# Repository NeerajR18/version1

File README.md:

# version1

version1 is a TKL(TenKeyLess) Mechanical Keyboard with Kalih Hotswappable sockets and Cherry MX Black switches.

The keyboard features a fully custom made PCB with 87 standard TKL keys and 4 macrokeys. The keyboard is wired, using a USB-C port.
version1 uses the STM32F072CBT6 at its core.

The PCB was designed in KiCad and the case was designed in Autodesk Fusion. Fusion was also used to render images of the design.
The footprints for the switches have been taken from the marbastlib library - https://github.com/ebastler/marbastlib

Made for Hack Club Fallout.
Note: This is still a WIP. Please copy anything at your own risk or do not copy at all.
## Why build this?
This keyboard was designed as a deep dive into electronics as a beginner and to learn more about CAD. 

I also have never used mechanical keyboards, so I want this to act as my entry point to mechanical keyboards.

## Repository Guide
```
version1/
|── PCB/
|   |── version1.kicad_pro
|   |── version1.kicad_pcb
|   |── version1.kicad_sch
|   └── version1_matrix.kicad_sch
|
|── CAD/
|   |── version1.f3d
|   |── version1-assembly.step
|   |── version1.fbx
|   |
|   |──── version1-base/
|   |     |── version1-base-left.step
|   |     |── version1-base-middle.step
|   |     └── version1-base-right.step
|   |
|   └──── version1-plate/
|         |── version1-plate-left.step
|         └── version1-plate-right.step
| 
|── Production/   
|    |── gerbers.zip/
|    |
|    |── STL Files/
|    |   |─── version1-base/
|    |   |    |── version1-base-left.stl
|    |   |    |── version1-base-middle.stl
|    |   |    └── version1-base-right.stl
|    |   |
|    |   └─── version1-plate/
|    |        |── version1-plate-left.stl
|    |        └── version1-plate-right.stl
|    |
|    └── STEP Files/
|           |─── version1-base/
|           |      |── version1-base-left.step
|           |      |── version1-base-middle.step
|           |      └── version1-base-right.step
|           |
|           └──── version1-plate/
|                   |── version1-plate-left.step
|                   └── version1-plate-right.step
|
|── Assets/
|    |── Keycaps/
|    |── MX Switch/
|    |── Rotary Encoder/
|    |── Type-C/
|    └── version1.fbx
|
|── qmk_firmware/
|    └── version1/
|       |── keymaps/
|       |   └── keymaps/
|       |       └── default/
|       |           └── keymap.c
|       |── config.h
|       |── keyboard.json
|       └── readme.md
|
|── BOM.csv
|── Zine.pdf
└── README.md
```

## Schematic
##### Overall Schematic

##### Key matrix

## PCB
##### PCB Front without GND Plane

##### PCB Front with GND Plane

##### PCB Back without GND Plane

##### PCB Back with GND Plane

## CAD
The case has been split into two parts on the plate and 3 parts on the base to accomodate 3D printed parts. The plates and base have small pegs and holes for assembly.

#### Full Assembly
##### Top View

#####  Side View

#### Top Plate
##### Top View

#####  Side View

#### Base
##### Top View

#####  Side View

## Renders 
##### Top view

##### Side view

## Build Guide
To be updated with pictures after IRL build.

## Bill of Materials

| MPN | Designator | Quantity | Unit Price (USD) | Price (Ext.) | Package | LCSC Part Number | Link |
|-----|------------|----------|-----------------|--------------|---------|-----------------|------|
| CPG151101S11-2 | MX1-M91 | 100 | 0.0344 | 3.44 | - | C49352235 | https://www.lcsc.com/product-detail/C49352235.html |
| STM32F072CBT6 | U1 | 1 | 2.212 | 2.21 | LQFP-48(7x7) | C81720 | https://www.lcsc.com/product-detail/C81720.html |
| XC6206P332MR-G | U2 | 5 | 0.1119 | 0.56 | SOT-23-3L | C5446 | https://www.lcsc.com/product-detail/C5446.html |
| PRTR5V0U2X-ES | D1 | 5 | 0.0404 | 0.2 | SOT-143 | C5180302 | https://www.lcsc.com/product-detail/C5180302.html |
| 1N4148W | D2-D93 | 100 | 0.0058 | 0.58 | SOD-123 | C917030 | https://www.lcsc.com/product-detail/C917030.html |
| TYPE-C 16PIN 2MD(073) | J1 | 20 | 0.0747 | 1.49 | SMD | C2765186 | https://www.lcsc.com/product-detail/C2765186.html |
| TS-1088-AR02016 | SW1, SW2 | 10 | 0.0538 | 0.54 | SMD, 4x3mm | C720477 | https://www.lcsc.com/product-detail/C720477.html |
| EC11E15244B2 | SW3 | 1 | 2 | 2 | Through Hole | C470754 | https://www.lcsc.com/product-detail/C470754.html |
| 1206L050YR | F1 | 10 | 0.0622 | 0.62 | 1206 | C163512 | https://www.lcsc.com/product-detail/C163512.html |
| RC0402FR-075K1L | R1, R2 | 100 | 0.0009 | 0.09 | 0402 | C105872 | https://www.lcsc.com/product-detail/C105872.html |
| RC0402FR-0710KL | R3 | 100 | 0.0008 | 0.08 | 0603 | C60490 | https://www.lcsc.com/product-detail/C60490.html |
| CC0402KRX7R7BB104 | C1, C4, C5, C6, C7, C8, C10 | 100 | 0.0011 | 0.11 | 0402 | C60474 | https://www.lcsc.com/product-detail/C60474.html |
| CL10B105KA8NNNC | C2, C3 | 50 | 0.0069 | 0.35 | 0603 | C29936 | https://www.lcsc.com/product-detail/C29936.html |
| CL10A106KP8NNNC | C9 | 50 | 0.0103 | 0.52 | 0603 | C19702 | https://www.lcsc.com/product-detail/C19702.html |
| Cherry MX Black Switches [Pack of 10] | - | 10 | 3.48 | 34.8 | - | - | https://neomacro.in/products/cherry-mx-switches?_pos=2&_sid=a9445e82d&_ss=r&variant=47150319108374 |
| Keycaps | - | 1 | 13.5 | 13.5 | - | - | https://stackskb.com/store/veekos-gradient-keycaps-cherry-profile-135-keys/ |
| Stabilizers (clip in) | - | 10 | 0.33 | 3.32 | - | - | https://neomacro.in/products/cherry-pcb-mount-stabilizers-clip-in?_pos=1&_sid=0547a7463&_ss=r |
| Wires for stabilizers | - | 1 | 4.16 | 4.16 | - | - | https://neomacro.in/products/equalz-c3-stabilizer-wire-set |
| M3x20mm Screws | - | 15 | 0.017 | 0.26 | - | - | https://omrook.com/ss-allen-csk-m3-x-20mm-dia-3mm-length-20mm-stainless-steel-ss202-allen-socket-countersunk-screws/ |
| M3x4 Brass Inserts | - | 50 | 0.023 | 1.15 | - | - | https://omrook.com/m3-x-4-brass-threaded-inserts-nut-50pc/ |
| Rotary Encoder Knob [Pack of 5] | - | 1 | 0.033 | 0.17 | - | - | https://makerbazar.in/products/black-rotary-encoder-knob-111-no |
| 1x4 Right Angle Berg Pin Header 2.54 mm pitch | J2 | 5 | 0.041 | 0.21 | - | - | https://sharvielectronics.com/product/4x1-4pin-male-right-angle-berg-header-connector-6mm-2-54mm-pitch/ |
| PCB - JLCPCB (with shipping) | - | 5 | 9.552 | 47.76 | - | - | https://jlcpcb.com/ |
| Total |  |  |  | 118.12 |  |  |  |

## Extras
### To be added in the future
- Angle adjustment
- Better case

### Resources I used for making this
- GrabCAD - https://grabcad.com/ [3D Models]
- marbastlib library - https://github.com/ebastler/marbastlib
- Noah Kiser on youtube - https://www.youtube.com/@noahkiser
- Keyboard Layout Editor - https://www.keyboard-layout-editor.com/
- ai03 Plate Generator - https://kbplate.ai03.com/
- MECH-TKL on cults3d - https://cults3d.com/en/3d-model/gadget/mechanical-keyboard-mech-tkl
- KiCad - https://www.kicad.org
- Keyboard Atelier discord server
- Autodesk Fusion - https://www.autodesk.com/products/fusion-360/personal
- Modern Hobbyist on YouTube - https://www.youtube.com/watch?v=u13yRbBiRYM
- iNimbleSloth on YouTube - https://www.youtube.com/watch?v=9bjp_LteX_Y
- Joe Scotto on YouTube - https://www.youtube.com/watch?v=o7SF2TPVV6o
- Hack Club and Fallout for funding - https://hackclub.com/
                                    - https://fallout.hackclub.com/

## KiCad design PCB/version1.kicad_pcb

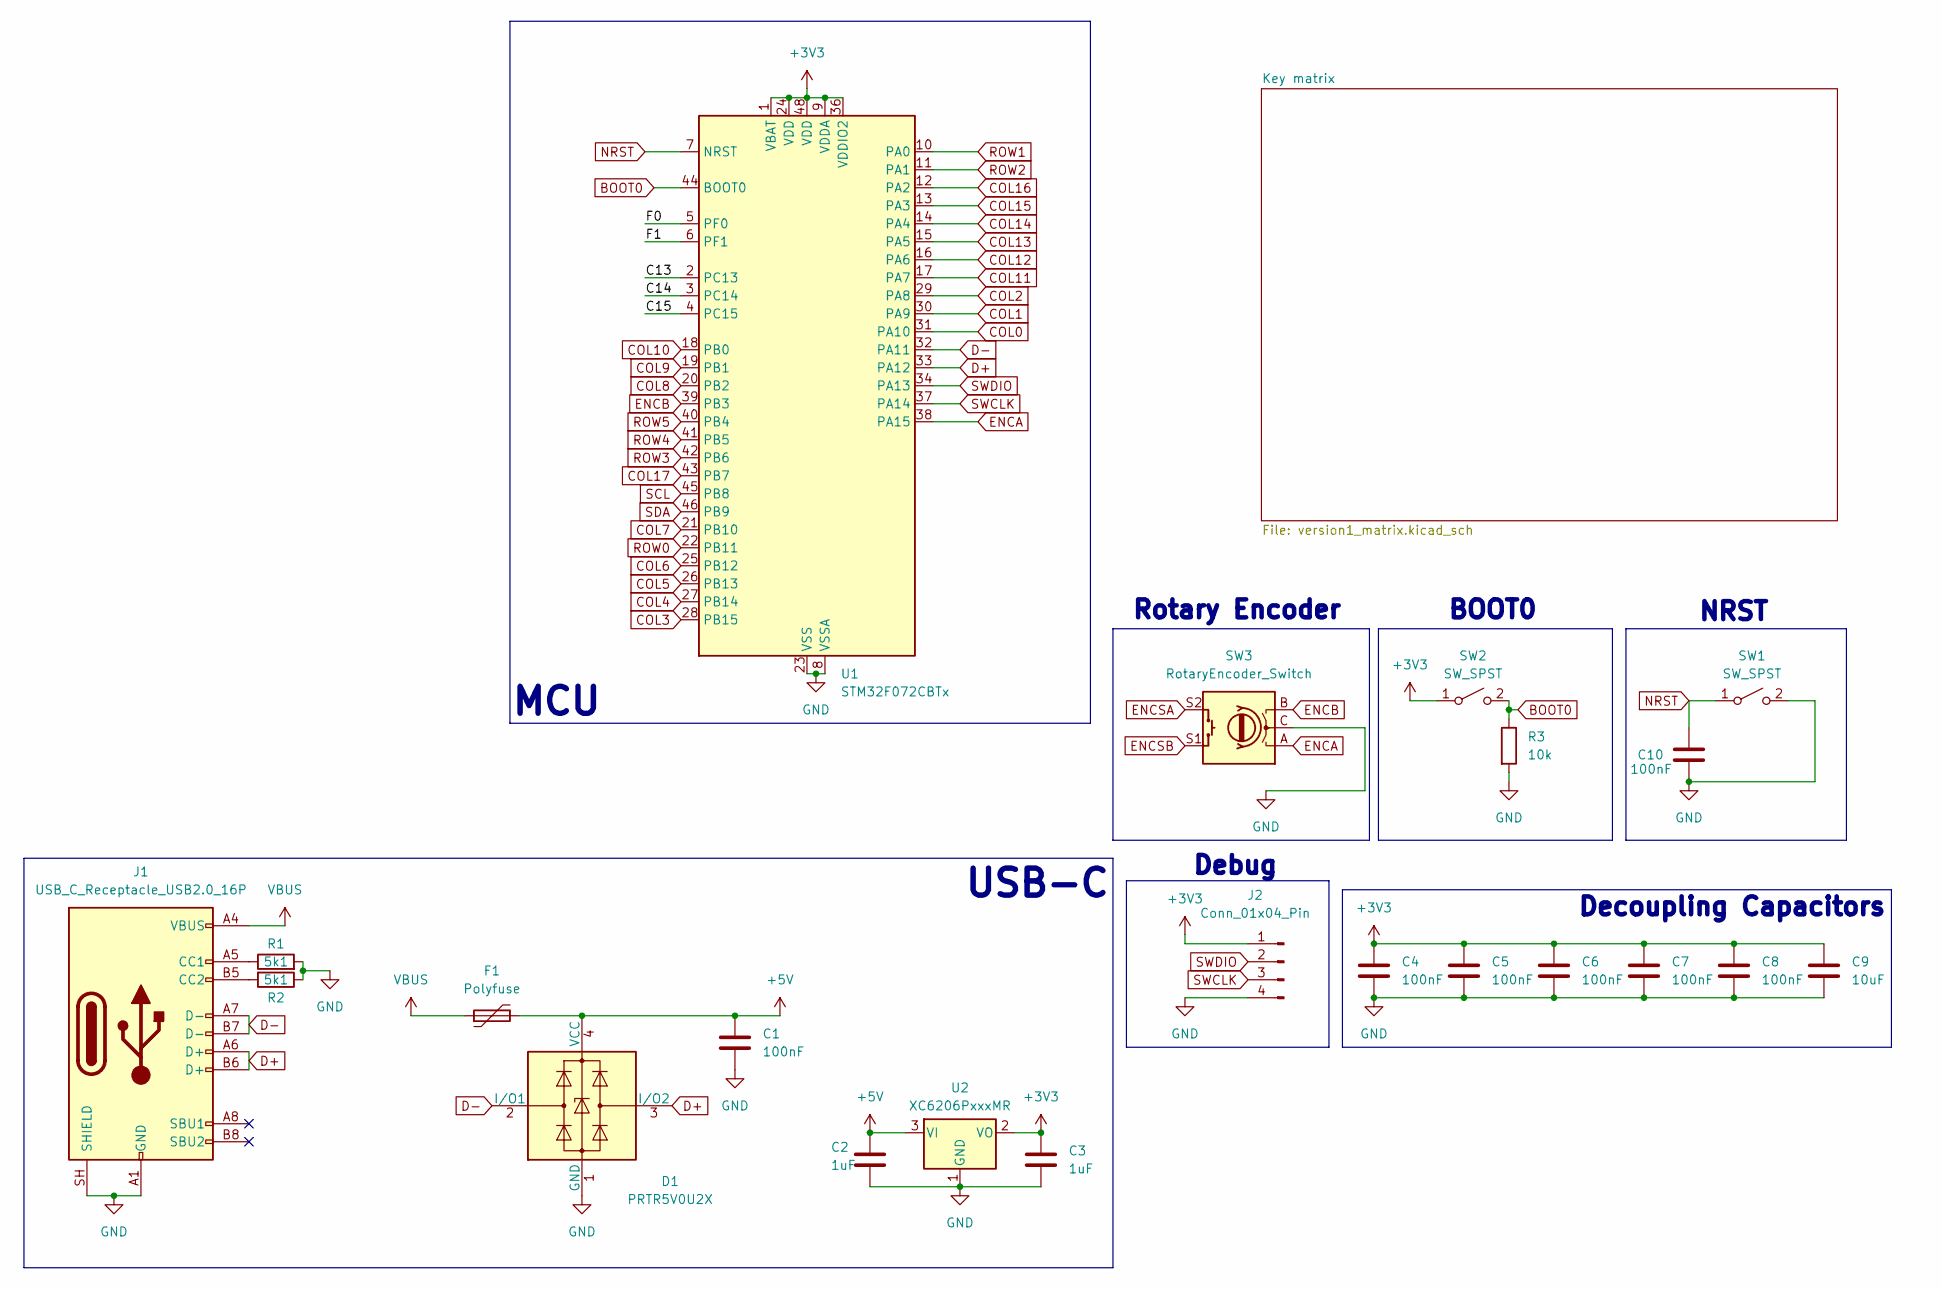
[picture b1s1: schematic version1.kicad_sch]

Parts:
C1, C4, C5, C6, C7, C8, C10: 100nF; C_0402_1005Metric
C2, C3: 1uF; C_0603_1608Metric
C9: 10uF; C_0603_1608Metric
D1: PRTR5V0U2X; SOT-143
F1: Polyfuse; Fuse_1206_3216Metric
J1: USB_C_Receptacle_USB2.0_16P; USB_C_Receptacle_HRO_TYPE-C-31-M-12
J2: Conn_01x04_Pin; PinHeader_1x04_P2.54mm_Horizontal
R1, R2: 5k1; R_0402_1005Metric
R3: 10k; R_0603_1608Metric
SW1, SW2: SW_SPST; SW_SPST_TS-1088-xR020
SW3: RotaryEncoder_Switch; RotaryEncoder_Alps_EC11E-Switch_Vertical_H20mm
U1: STM32F072CBTx; LQFP-48_7x7mm_P0.5mm
U2: XC6206PxxxMR; SOT-23-3

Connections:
+3V3: C3.1, C4.1, C5.1, C6.1, C7.1, C8.1, C9.1, J2.1, SW2.1 (A), U1.1 (VBAT), U1.9 (VDDA), U1.24 (VDD), U1.36 (VDDIO2), U1.48 (VDD), U2.2 (VO)
+5V: C1.1, C2.1, D1.4 (VCC), F1.2, U2.3 (VI)
/C13: U1.2 (PC13)
/C14: U1.3 (PC14)
/C15: U1.4 (PC15)
/F0: U1.5 (PF0)
/F1: U1.6 (PF1)
BOOT0: R3.1, SW2.2 (B), U1.44 (BOOT0)
COL0: U1.31 (PA10); also elsewhere on the board
COL1: U1.30 (PA9); also elsewhere on the board
COL2: U1.29 (PA8); also elsewhere on the board
COL3: U1.28 (PB15); also elsewhere on the board
COL4: U1.27 (PB14); also elsewhere on the board
COL5: U1.26 (PB13); also elsewhere on the board
COL6: U1.25 (PB12); also elsewhere on the board
COL7: U1.21 (PB10); also elsewhere on the board
COL8: U1.20 (PB2); also elsewhere on the board
COL9: U1.19 (PB1); also elsewhere on the board
COL10: U1.18 (PB0); also elsewhere on the board
COL11: U1.17 (PA7); also elsewhere on the board
COL12: U1.16 (PA6); also elsewhere on the board
COL13: U1.15 (PA5); also elsewhere on the board
COL14: U1.14 (PA4); also elsewhere on the board
COL15: U1.13 (PA3); also elsewhere on the board
COL16: U1.12 (PA2); also elsewhere on the board
COL17: SW3.S1, U1.43 (PB7); also elsewhere on the board
D+: D1.3 (I/O2), J1.A6 (D+), J1.B6 (D+), U1.33 (PA12)
D-: D1.2 (I/O1), J1.A7 (D-), J1.B7 (D-), U1.32 (PA11)
ENCA: SW3.A, U1.38 (PA15)
ENCB: SW3.B, U1.39 (PB3)
ENCSA: SW3.S2; also elsewhere on the board
GND: C1.2, C2.2, C3.2, C4.2, C5.2, C6.2, C7.2, C8.2, C9.2, C10.2, D1.1 (GND), J1.A1 (GND), J1.A12 (GND), J1.B1 (GND), J1.B12 (GND), J1.SH (SHIELD), J2.4, R1.2, R2.1, R3.2, SW1.2 (B), SW3.C, U1.8 (VSSA), U1.23 (VSS), U1.35 (VSS), U1.47 (VSS), U2.1 (GND)
NRST: C10.1, SW1.1 (A), U1.7 (NRST)
unnamed: J1.A5 (CC1), R1.1
unnamed: J1.B5 (CC2), R2.2
ROW0: U1.22 (PB11); also elsewhere on the board
ROW1: U1.10 (PA0); also elsewhere on the board
ROW2: U1.11 (PA1); also elsewhere on the board
ROW3: U1.42 (PB6); also elsewhere on the board
ROW4: U1.41 (PB5); also elsewhere on the board
ROW5: U1.40 (PB4); also elsewhere on the board
SCL: U1.45 (PB8)
SDA: U1.46 (PB9)
SWCLK: J2.3, U1.37 (PA14)
SWDIO: J2.2, U1.34 (PA13)
VBUS: F1.1, J1.A4 (VBUS), J1.A9 (VBUS), J1.B4 (VBUS), J1.B9 (VBUS)

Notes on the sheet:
BOOT0
Debug
MCU
Rotary Encoder
NRST
USB-C
Decoupling Capacitors

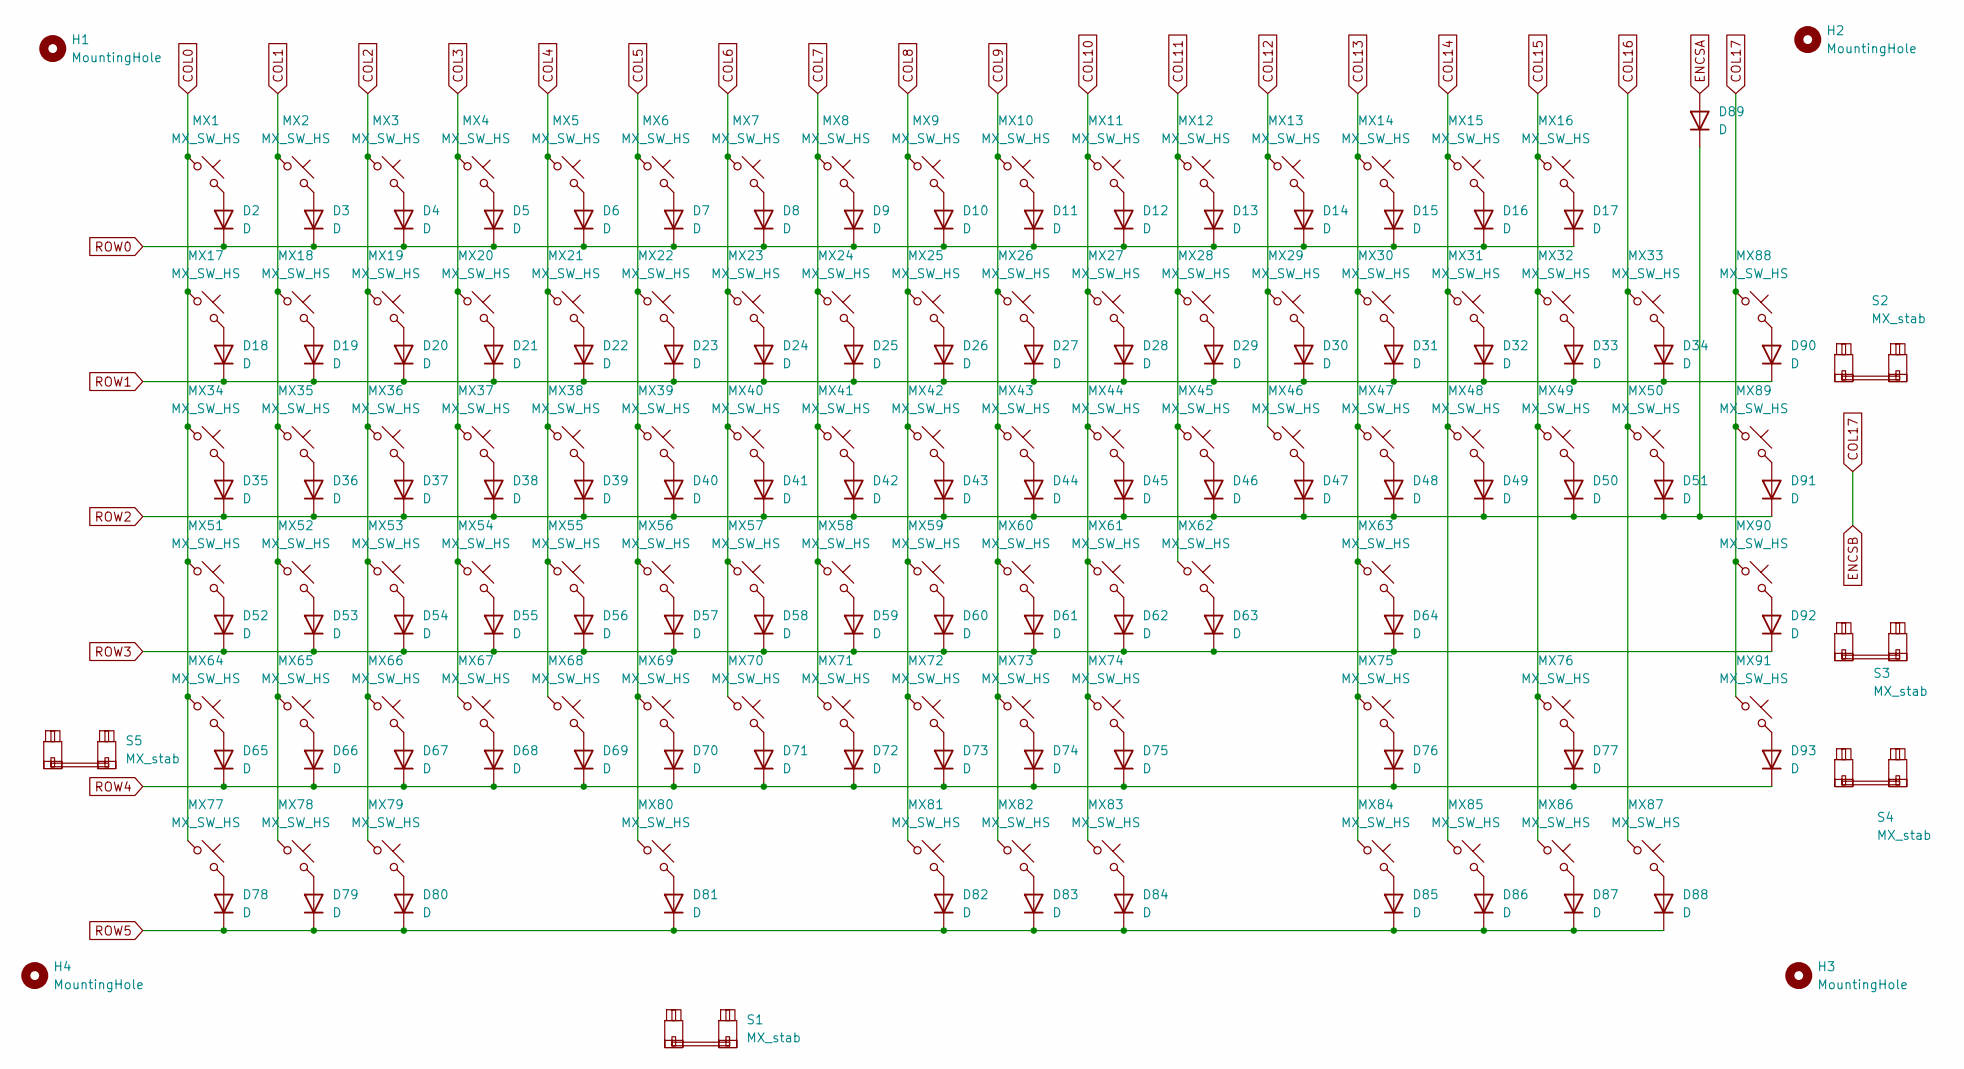
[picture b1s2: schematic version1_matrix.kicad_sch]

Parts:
D2, D3, D4, D5, D6, D7, D8, D9, D10, D11, D12, D13, D14, D15, D16, D17, D18, D19, D20, D21, D22, D23, D24, D25, D26, D27, D28, D29, D30, D31, D32, D33, D34, D35, D36, D37, D38, D39, D40, D41, D42, D43, D44, D45, D46, D47, D48, D49, D50, D51, D52, D53, D54, D55, D56, D57, D58, D59, D60, D61, D62, D63, D64, D65, D66, D67, D68, D69, D70, D71, D72, D73, D74, D75, D76, D77, D78, D79, D80, D81, D82, D83, D84, D85, D86, D87, D88, D89, D90, D91, D92, D93: D; D_SOD-123
H1, H2, H3, H4: MountingHole; MountingHole_2mm
MX1, MX2, MX3, MX4, MX5, MX6, MX7, MX8, MX9, MX10, MX11, MX12, MX13, MX14, MX15, MX16, MX17, MX18, MX19, MX20, MX21, MX22, MX23, MX24, MX25, MX26, MX27, MX28, MX29, MX30, MX31, MX32, MX33, MX35, MX36, MX37, MX38, MX39, MX40, MX41, MX42, MX43, MX44, MX45, MX46, MX48, MX49, MX50, MX52, MX53, MX54, MX55, MX56, MX57, MX58, MX59, MX60, MX61, MX62, MX63, MX64, MX65, MX66, MX67, MX68, MX69, MX70, MX71, MX72, MX73, MX74, MX75, MX76, MX80, MX85, MX86, MX87, MX88, MX89, MX90, MX91: MX_SW_HS; SW_MX_HS_CPG151101S11_1u
MX34, MX47: MX_SW_HS; SW_MX_HS_CPG151101S11_1.5u
MX51: MX_SW_HS; SW_MX_HS_CPG151101S11_1.75u
MX77, MX78, MX79, MX81, MX82, MX83, MX84: MX_SW_HS; SW_MX_HS_CPG151101S11_1.25u
S1: MX_stab; STAB_MX_6.25u
S2, S3: MX_stab; STAB_MX_2.25u
S4: MX_stab; STAB_MX_2.75u
S5: MX_stab; STAB_MX_2u

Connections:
COL0: MX1.1, MX17.1, MX34.1, MX51.1, MX64.1, MX77.1; also elsewhere on the board
COL1: MX2.1, MX18.1, MX35.1, MX52.1, MX65.1, MX78.1; also elsewhere on the board
COL2: MX3.1, MX19.1, MX36.1, MX53.1, MX66.1, MX79.1; also elsewhere on the board
COL3: MX4.1, MX20.1, MX37.1, MX54.1, MX67.1; also elsewhere on the board
COL4: MX5.1, MX21.1, MX38.1, MX55.1, MX68.1; also elsewhere on the board
COL5: MX6.1, MX22.1, MX39.1, MX56.1, MX69.1, MX80.1; also elsewhere on the board
COL6: MX7.1, MX23.1, MX40.1, MX57.1, MX70.1; also elsewhere on the board
COL7: MX8.1, MX24.1, MX41.1, MX58.1, MX71.1; also elsewhere on the board
COL8: MX9.1, MX25.1, MX42.1, MX59.1, MX72.1, MX81.1; also elsewhere on the board
COL9: MX10.1, MX26.1, MX43.1, MX60.1, MX73.1, MX82.1; also elsewhere on the board
COL10: MX11.1, MX27.1, MX44.1, MX61.1, MX74.1, MX83.1; also elsewhere on the board
COL11: MX12.1, MX28.1, MX45.1, MX62.1; also elsewhere on the board
COL12: MX13.1, MX29.1, MX46.1; also elsewhere on the board
COL13: MX14.1, MX30.1, MX47.1, MX63.1, MX75.1, MX84.1; also elsewhere on the board
COL14: MX15.1, MX31.1, MX48.1, MX85.1; also elsewhere on the board
COL15: MX16.1, MX32.1, MX49.1, MX76.1, MX86.1; also elsewhere on the board
COL16: MX33.1, MX50.1, MX87.1; also elsewhere on the board
COL17: MX88.1, MX89.1, MX90.1, MX91.1; also elsewhere on the board
ENCSA: D89.2 (A); also elsewhere on the board
unnamed: D2.2 (A), MX1.2
unnamed: D3.2 (A), MX2.2
unnamed: D4.2 (A), MX3.2
unnamed: D5.2 (A), MX4.2
unnamed: D6.2 (A), MX5.2
unnamed: D7.2 (A), MX6.2
unnamed: D8.2 (A), MX7.2
unnamed: D9.2 (A), MX8.2
unnamed: D10.2 (A), MX9.2
unnamed: D11.2 (A), MX10.2
unnamed: D12.2 (A), MX11.2
unnamed: D13.2 (A), MX12.2
unnamed: D14.2 (A), MX13.2
unnamed: D15.2 (A), MX14.2
unnamed: D16.2 (A), MX15.2
unnamed: D17.2 (A), MX16.2
unnamed: D18.2 (A), MX17.2
unnamed: D19.2 (A), MX18.2
unnamed: D20.2 (A), MX19.2
unnamed: D21.2 (A), MX20.2
unnamed: D22.2 (A), MX21.2
unnamed: D23.2 (A), MX22.2
unnamed: D24.2 (A), MX23.2
unnamed: D25.2 (A), MX24.2
unnamed: D26.2 (A), MX25.2
unnamed: D27.2 (A), MX26.2
unnamed: D28.2 (A), MX27.2
unnamed: D29.2 (A), MX28.2
unnamed: D30.2 (A), MX29.2
unnamed: D31.2 (A), MX30.2
unnamed: D32.2 (A), MX31.2
unnamed: D33.2 (A), MX32.2
unnamed: D34.2 (A), MX33.2
unnamed: D35.2 (A), MX34.2
unnamed: D36.2 (A), MX35.2
unnamed: D37.2 (A), MX36.2
unnamed: D38.2 (A), MX37.2
unnamed: D39.2 (A), MX38.2
unnamed: D40.2 (A), MX39.2
unnamed: D41.2 (A), MX40.2
unnamed: D42.2 (A), MX41.2
unnamed: D43.2 (A), MX42.2
unnamed: D44.2 (A), MX43.2
unnamed: D45.2 (A), MX44.2
unnamed: D46.2 (A), MX45.2
unnamed: D47.2 (A), MX46.2
unnamed: D48.2 (A), MX47.2
unnamed: D49.2 (A), MX48.2
unnamed: D50.2 (A), MX49.2
unnamed: D51.2 (A), MX50.2
unnamed: D52.2 (A), MX51.2
unnamed: D53.2 (A), MX52.2
unnamed: D54.2 (A), MX53.2
unnamed: D55.2 (A), MX54.2
unnamed: D56.2 (A), MX55.2
unnamed: D57.2 (A), MX56.2
unnamed: D58.2 (A), MX57.2
unnamed: D59.2 (A), MX58.2
unnamed: D60.2 (A), MX59.2
unnamed: D61.2 (A), MX60.2
unnamed: D62.2 (A), MX61.2
unnamed: D63.2 (A), MX62.2
unnamed: D64.2 (A), MX63.2
unnamed: D65.2 (A), MX64.2
unnamed: D66.2 (A), MX65.2
unnamed: D67.2 (A), MX66.2
unnamed: D68.2 (A), MX67.2
unnamed: D69.2 (A), MX68.2
unnamed: D70.2 (A), MX69.2
unnamed: D71.2 (A), MX70.2
unnamed: D72.2 (A), MX71.2
unnamed: D73.2 (A), MX72.2
unnamed: D74.2 (A), MX73.2
unnamed: D75.2 (A), MX74.2
unnamed: D76.2 (A), MX75.2
unnamed: D77.2 (A), MX76.2
unnamed: D78.2 (A), MX77.2
unnamed: D79.2 (A), MX78.2
unnamed: D80.2 (A), MX79.2
unnamed: D81.2 (A), MX80.2
unnamed: D82.2 (A), MX81.2
unnamed: D83.2 (A), MX82.2
unnamed: D84.2 (A), MX83.2
unnamed: D85.2 (A), MX84.2
unnamed: D86.2 (A), MX85.2
unnamed: D87.2 (A), MX86.2
unnamed: D88.2 (A), MX87.2
unnamed: D90.2 (A), MX88.2
unnamed: D91.2 (A), MX89.2
unnamed: D92.2 (A), MX90.2
unnamed: D93.2 (A), MX91.2
ROW0: D2.1 (K), D3.1 (K), D4.1 (K), D5.1 (K), D6.1 (K), D7.1 (K), D8.1 (K), D9.1 (K), D10.1 (K), D11.1 (K), D12.1 (K), D13.1 (K), D14.1 (K), D15.1 (K), D16.1 (K), D17.1 (K); also elsewhere on the board
ROW1: D18.1 (K), D19.1 (K), D20.1 (K), D21.1 (K), D22.1 (K), D23.1 (K), D24.1 (K), D25.1 (K), D26.1 (K), D27.1 (K), D28.1 (K), D29.1 (K), D30.1 (K), D31.1 (K), D32.1 (K), D33.1 (K), D34.1 (K), D90.1 (K); also elsewhere on the board
ROW2: D35.1 (K), D36.1 (K), D37.1 (K), D38.1 (K), D39.1 (K), D40.1 (K), D41.1 (K), D42.1 (K), D43.1 (K), D44.1 (K), D45.1 (K), D46.1 (K), D47.1 (K), D48.1 (K), D49.1 (K), D50.1 (K), D51.1 (K), D89.1 (K), D91.1 (K); also elsewhere on the board
ROW3: D52.1 (K), D53.1 (K), D54.1 (K), D55.1 (K), D56.1 (K), D57.1 (K), D58.1 (K), D59.1 (K), D60.1 (K), D61.1 (K), D62.1 (K), D63.1 (K), D64.1 (K), D92.1 (K); also elsewhere on the board
ROW4: D65.1 (K), D66.1 (K), D67.1 (K), D68.1 (K), D69.1 (K), D70.1 (K), D71.1 (K), D72.1 (K), D73.1 (K), D74.1 (K), D75.1 (K), D76.1 (K), D77.1 (K), D93.1 (K); also elsewhere on the board
ROW5: D78.1 (K), D79.1 (K), D80.1 (K), D81.1 (K), D82.1 (K), D83.1 (K), D84.1 (K), D85.1 (K), D86.1 (K), D87.1 (K), D88.1 (K); also elsewhere on the board

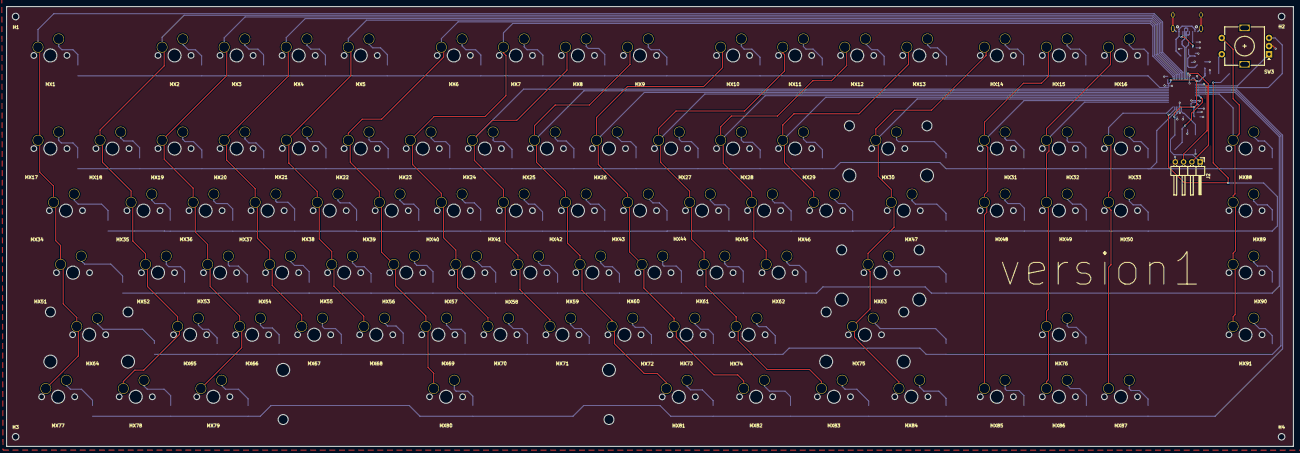
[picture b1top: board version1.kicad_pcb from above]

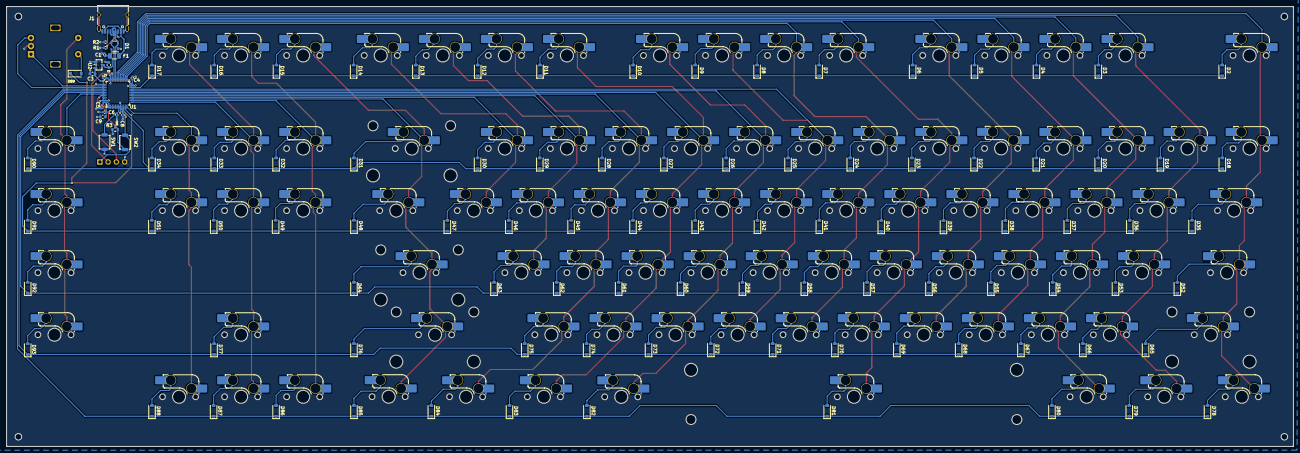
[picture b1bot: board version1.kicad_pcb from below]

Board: 2 copper layers, 395.0 x 135.0 mm, 214 parts (203 on the bottom side), 130 nets.

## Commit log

2026-05-15 Added folders and PCB files
    Added KiCad PCB files along with gerbers
2026-05-16 Updated PCB and gerbers
2026-05-21 Added CAD files
2026-05-21 PCB and gerbers with BOM
    Added KiCad Project files along with gerbers for production and Bill of Materials
2026-05-22 Added 3D models for keycaps
2026-05-27 Added updated CAD files and BOM.csv
2026-05-28 Updated PCB, gerbers and added STEP files to production folder
2026-05-28 Added stl files and other 3d models
2026-05-28 Updated schematic
2026-05-28 Added firmware files
2026-05-28 Updated BOM.csv
2026-05-29 Updated BOM and readme
2026-05-29 Update README with renders and small improvments
2026-05-29 Added Zine.pdf
2026-05-29 Added links to resources and Zine page
2026-06-02 Updated PCB files
2026-06-02 Updated PCB images and BOM
2026-06-02 minor changes
2026-06-03 Minor PCB silkscreen changes with updated gerbers
